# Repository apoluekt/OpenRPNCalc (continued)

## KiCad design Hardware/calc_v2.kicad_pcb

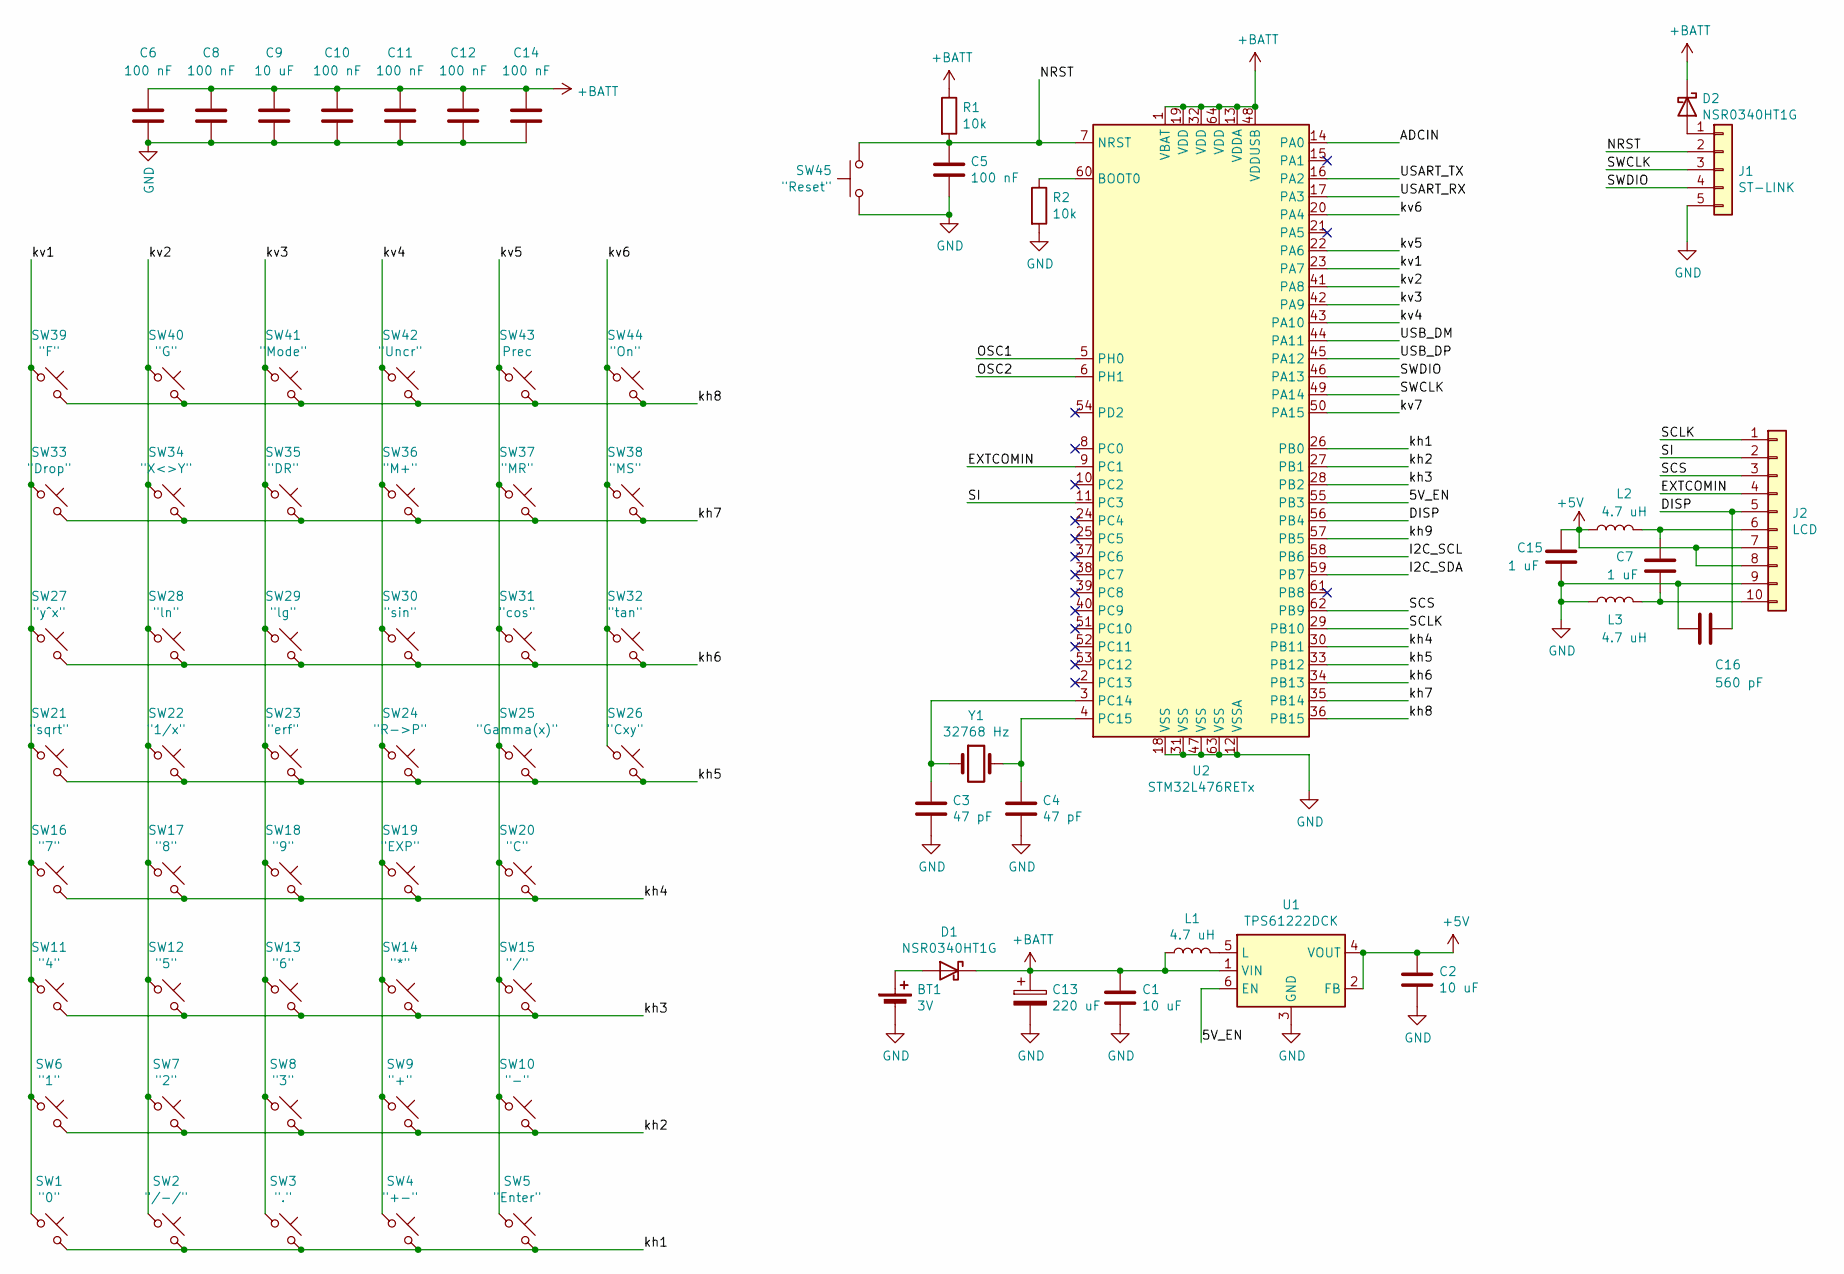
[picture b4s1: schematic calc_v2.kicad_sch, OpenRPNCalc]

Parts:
BT1: 3V; BatteryHolder_Keystone_1057_1x2032
C1, C2, C9: 10 uF; C_0603_1608Metric_Pad1.08x0.95mm_HandSolder
C3, C4: 47 pF; C_0603_1608Metric_Pad1.08x0.95mm_HandSolder
C5, C6, C8, C10, C11, C12, C14: 100 nF; C_0603_1608Metric_Pad1.08x0.95mm_HandSolder
C7, C15: 1 uF; C_0603_1608Metric_Pad1.08x0.95mm_HandSolder
C13: 220 uF; CP_EIA-3528-21_Kemet-B_Pad1.50x2.35mm_HandSolder
C16: 560 pF; C_0603_1608Metric_Pad1.08x0.95mm_HandSolder
D1, D2: NSR0340HT1G; D_0603_1608Metric_Pad1.05x0.95mm_HandSolder
J1: ST-LINK; PinHeader_1x05_P2.54mm_Horizontal
J2: LCD; Molex_1x10_P0.50mm_Horizontal
L1, L2, L3: 4.7 uH; L_0805_2012Metric_Pad1.15x1.40mm_HandSolder
R1, R2: 10k; R_0603_1608Metric_Pad0.98x0.95mm_HandSolder
SW1: "0"; SW_SPST_EVQQ2
SW2: "/-/"; SW_SPST_EVQQ2
SW3: "."; SW_SPST_EVQQ2
SW4: "+-"; SW_SPST_EVQQ2
SW5: "Enter"; SW_SPST_EVQQ2
SW6: "1"; SW_SPST_EVQQ2
SW7: "2"; SW_SPST_EVQQ2
SW8: "3"; SW_SPST_EVQQ2
SW9: "+"; SW_SPST_EVQQ2
SW10: "-"; SW_SPST_EVQQ2
SW11: "4"; SW_SPST_EVQQ2
SW12: "5"; SW_SPST_EVQQ2
SW13: "6"; SW_SPST_EVQQ2
SW14: "*"; SW_SPST_EVQQ2
SW15: "/"; SW_SPST_EVQQ2
SW16: "7"; SW_SPST_EVQQ2
SW17: "8"; SW_SPST_EVQQ2
SW18: "9"; SW_SPST_EVQQ2
SW19: "EXP"; SW_SPST_EVQQ2
SW20: "C"; SW_SPST_EVQQ2
SW21: "sqrt"; SW_SPST_EVQQ2
SW22: "1/x"; SW_SPST_EVQQ2
SW23: "erf"; SW_SPST_EVQQ2
SW24: "R->P"; SW_SPST_EVQQ2
SW25: "Gamma(x)"; SW_SPST_EVQQ2
SW26: "Cxy"; SW_SPST_EVQQ2
SW27: "y^x"; SW_SPST_EVQQ2
SW28: "ln"; SW_SPST_EVQQ2
SW29: "lg"; SW_SPST_EVQQ2
SW30: "sin"; SW_SPST_EVQQ2
SW31: "cos"; SW_SPST_EVQQ2
SW32: "tan"; SW_SPST_EVQQ2
SW33: "Drop"; SW_SPST_EVQQ2
SW34: "X<>Y"; SW_SPST_EVQQ2
SW35: "DR"; SW_SPST_EVQQ2
SW36: "M+"; SW_SPST_EVQQ2
SW37: "MR"; SW_SPST_EVQQ2
SW38: "MS"; SW_SPST_EVQQ2
SW39: "F"; SW_SPST_EVQQ2
SW40: "G"; SW_SPST_EVQQ2
SW41: "Mode"; SW_SPST_EVQQ2
SW42: "Uncr"; SW_SPST_EVQQ2
SW43: Prec; SW_SPST_EVQQ2
SW44: "On"; SW_SPST_EVQQ2
SW45: "Reset"; SW_SPST_EVQQ2
U1: TPS61222DCK; Texas_R-PDSO-G6
U2: STM32L476RETx; LQFP-64_10x10mm_P0.5mm
Y1: 32768 Hz; Crystal_SMD_2012-2Pin_2.0x1.2mm_HandSoldering

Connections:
+5V: C2.1, C15.1, J2.7, J2.8, L2.1, U1.2 (FB), U1.4 (VOUT)
+BATT: C1.1, C6.2, C8.2, C9.2, C10.2, C11.2, C12.2, C13.1, C14.2, D1.1 (K), D2.1 (K), L1.1, R1.1, U1.1 (VIN), U2.1 (VBAT), U2.13 (VDDA), U2.19 (VDD), U2.32 (VDD), U2.48 (VDDUSB), U2.64 (VDD)
/5V_EN: U1.6 (EN), U2.55 (PB3)
/ADCIN: U2.14 (PA0)
/DISP: C16.1, J2.5, U2.56 (PB4)
/EXTCOMIN: J2.4, U2.9 (PC1)
/I2C_SCL: U2.58 (PB6)
/I2C_SDA: U2.59 (PB7)
/NRST: C5.1, J1.2, R1.2, SW45.1, U2.7 (NRST)
/OSC1: U2.5 (PH0)
/OSC2: U2.6 (PH1)
/SCLK: J2.1, U2.29 (PB10)
/SCS: J2.3, U2.62 (PB9)
/SI: J2.2, U2.11 (PC3)
/SWCLK: J1.3, U2.49 (PA14)
/SWDIO: J1.4, U2.46 (PA13)
/USART_RX: U2.17 (PA3)
/USART_TX: U2.16 (PA2)
/USB_DM: U2.44 (PA11)
/USB_DP: U2.45 (PA12)
/kh1: SW1.2, SW2.2, SW3.2, SW4.2, SW5.2, U2.26 (PB0)
/kh2: SW6.2, SW7.2, SW8.2, SW9.2, SW10.2, U2.27 (PB1)
/kh3: SW11.2, SW12.2, SW13.2, SW14.2, SW15.2, U2.28 (PB2)
/kh4: SW16.2, SW17.2, SW18.2, SW19.2, SW20.2, U2.30 (PB11)
/kh5: SW21.2, SW22.2, SW23.2, SW24.2, SW25.2, SW26.2, U2.33 (PB12)
/kh6: SW27.2, SW28.2, SW29.2, SW30.2, SW31.2, SW32.2, U2.34 (PB13)
/kh7: SW33.2, SW34.2, SW35.2, SW36.2, SW37.2, SW38.2, U2.35 (PB14)
/kh8: SW39.2, SW40.2, SW41.2, SW42.2, SW43.2, SW44.2, U2.36 (PB15)
/kh9: U2.57 (PB5)
/kv1: SW1.1, SW6.1, SW11.1, SW16.1, SW21.1, SW27.1, SW33.1, SW39.1, U2.23 (PA7)
/kv2: SW2.1, SW7.1, SW12.1, SW17.1, SW22.1, SW28.1, SW34.1, SW40.1, U2.41 (PA8)
/kv3: SW3.1, SW8.1, SW13.1, SW18.1, SW23.1, SW29.1, SW35.1, SW41.1, U2.42 (PA9)
/kv4: SW4.1, SW9.1, SW14.1, SW19.1, SW24.1, SW30.1, SW36.1, SW42.1, U2.43 (PA10)
/kv5: SW5.1, SW10.1, SW15.1, SW20.1, SW25.1, SW31.1, SW37.1, SW43.1, U2.22 (PA6)
/kv6: SW26.1, SW32.1, SW38.1, SW44.1, U2.20 (PA4)
/kv7: U2.50 (PA15)
GND: BT1.2 (-), C1.2, C2.2, C3.2, C4.2, C5.2, C6.1, C8.1, C9.1, C10.1, C11.1, C12.1, C13.2, C14.1, C15.2, C16.2, J1.5, J2.9, L3.1, R2.2, SW45.2, U1.3 (GND), U2.12 (VSSA), U2.18 (VSS), U2.31 (VSS), U2.47 (VSS), U2.63 (VSS)
unnamed: BT1.1 (+), D1.2 (A)
unnamed: D2.2 (A), J1.1
unnamed: C7.1, J2.6, L2.2
unnamed: C7.2, J2.10, L3.2
unnamed: L1.2, U1.5 (L)
unnamed: R2.1, U2.60 (BOOT0)
unnamed: C3.1, U2.3 (PC14), Y1.1
unnamed: C4.1, U2.4 (PC15), Y1.2

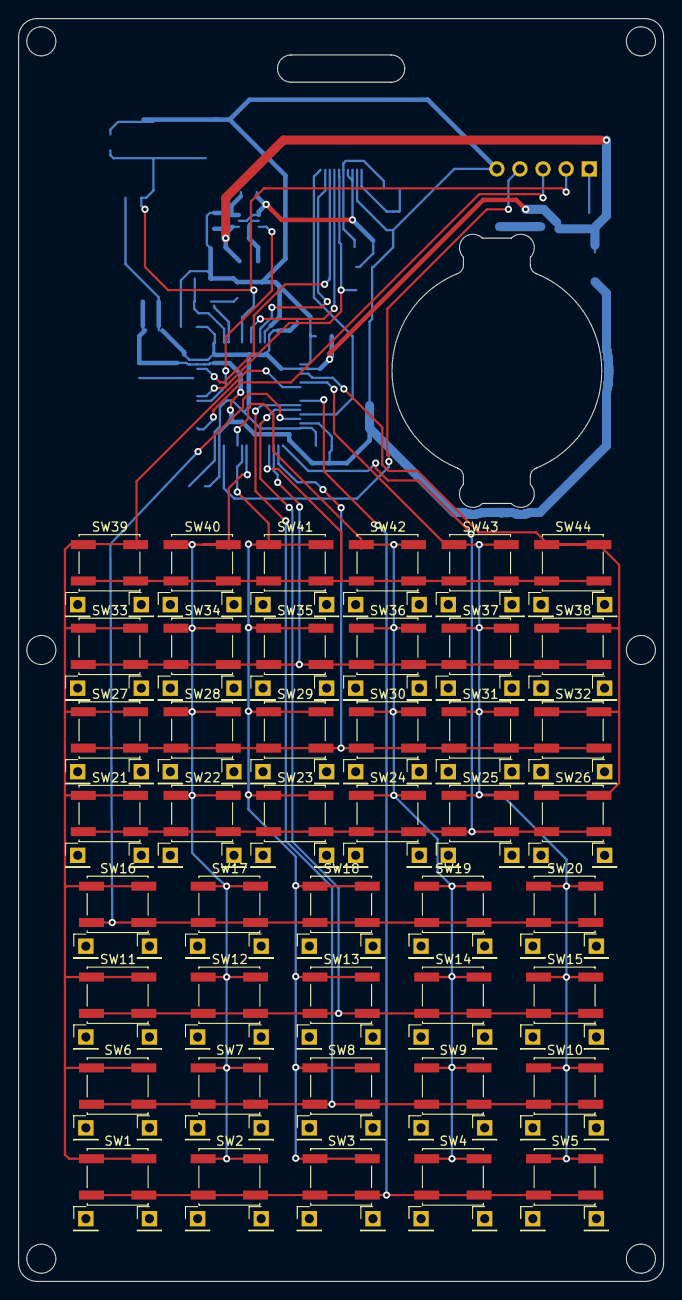
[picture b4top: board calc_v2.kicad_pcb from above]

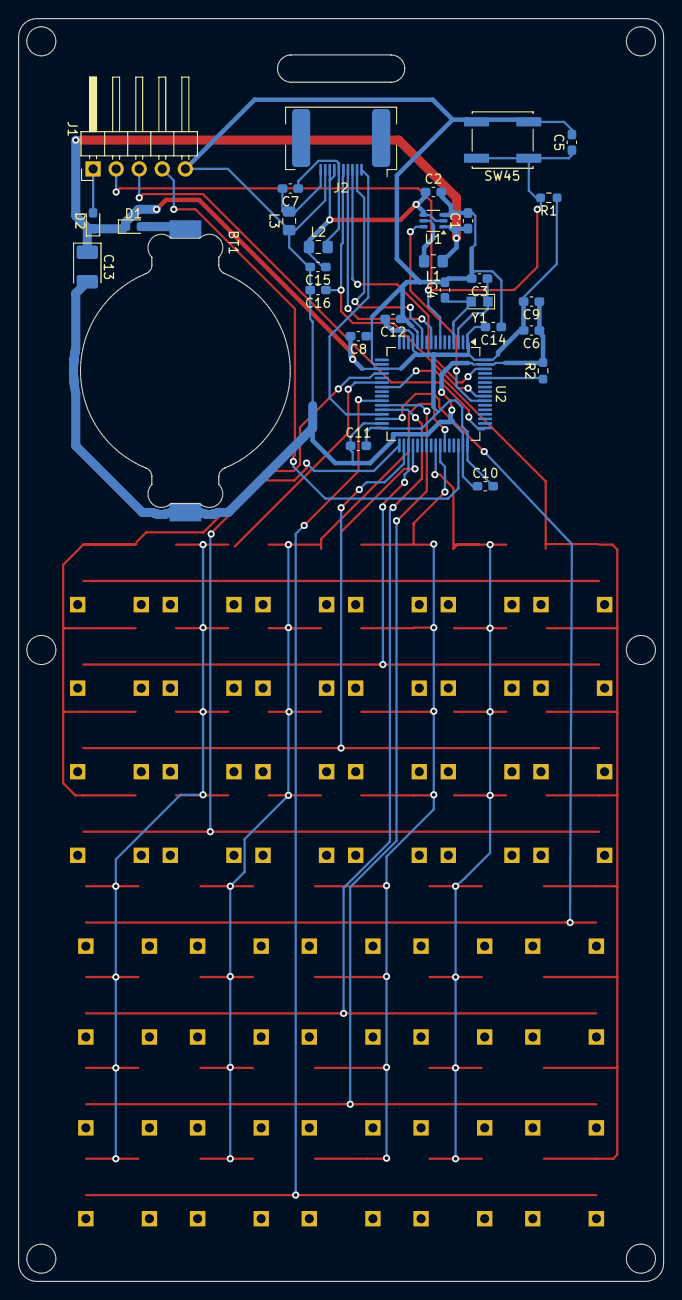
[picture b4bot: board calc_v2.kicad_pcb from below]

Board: 2 copper layers, 71.0 x 139.0 mm, 162 parts (30 on the bottom side), 34 nets.

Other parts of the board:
P1a, P1b, P2a, P2b, P3a, P3b, P4a, P4b, P5a, P5b, P6a, P6b, P7a, P7b, P8a, P8b, P9a, P9b, P10a, P10b, P11a, P11b, P12a, P12b, P13a, P13b, P14a, P14b, P15a, P15b, P16a, P16b, P17a, P17b, P18a, P18b, P19a, P19b, P20a, P20b, P21a, P21b, P22a, P22b, P23a, P23b, P24a, P24b, P25a, P25b, P26a, P26b, P27a, P27b, P28a, P28b, P29a, P29b, P30a, P30b, P31a, P31b, P32a, P32b, P33a, P33b, P34a, P34b, P35a, P35b, P36a, P36b, P37a, P37b, P38a, P38b, P39a, P39b, P40a, P40b, P41a, P41b, P42a, P42b, P43a, P43b, P44a, P44b: PinHeader_1x01_P2.54mm_Vertical

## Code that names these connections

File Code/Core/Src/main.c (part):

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		if (keycode == 54 && off && last_keycode == 0) {  // Calculator was OFF and the ON button was pressed
			HAL_GPIO_WritePin(GPIOA, GPIO_PIN_15, GPIO_PIN_SET); // 5V booster enable
			HAL_Delay(1); // Wait while 5V rises
			HAL_GPIO_WritePin(GPIOA, GPIO_PIN_10, GPIO_PIN_SET); // DISP signal to "ON"
			delay_us(30);
			keycode = 0;
			off = 0;
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
			if (!ret) {  // OFF command received
				delay_us(30);
				HAL_GPIO_WritePin(GPIOA, GPIO_PIN_10, GPIO_PIN_RESET);  // DISP signal to "OFF"
				delay_us(30);
				HAL_GPIO_WritePin(GPIOA, GPIO_PIN_9, GPIO_PIN_RESET);   // EXTCOMIN signal of "OFF"
				HAL_GPIO_WritePin(GPIOA, GPIO_PIN_15, GPIO_PIN_RESET);  // 5V booster disable
				off = 1;
			}
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  /*Configure GPIO pin Output Level */
  HAL_GPIO_WritePin(GPIOD, GPIO_PIN_2, GPIO_PIN_RESET);

  /*Configure GPIO pins : PC13 PC14 PC15 PC8
                           PC9 PC10 PC11 PC12 */
  GPIO_InitStruct.Pin = GPIO_PIN_13|GPIO_PIN_14|GPIO_PIN_15|GPIO_PIN_8
                          |GPIO_PIN_9|GPIO_PIN_10|GPIO_PIN_11|GPIO_PIN_12;
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  GPIO_InitStruct.Pull = GPIO_NOPULL;
  HAL_GPIO_Init(GPIOC, &GPIO_InitStruct);

  /*Configure GPIO pins : PH0 PH1 PH3 */
  GPIO_InitStruct.Pin = GPIO_PIN_0|GPIO_PIN_1|GPIO_PIN_3;
  GPIO_InitStruct.Mode = GPIO_MODE_ANALOG;
  GPIO_InitStruct.Pull = GPIO_NOPULL;
  HAL_GPIO_Init(GPIOH, &GPIO_InitStruct);

  /*Configure GPIO pin : PC0 */
  GPIO_InitStruct.Pin = GPIO_PIN_0;
  GPIO_InitStruct.Mode = GPIO_MODE_OUTPUT_PP;
  GPIO_InitStruct.Pull = GPIO_NOPULL;
  GPIO_InitStruct.Speed = GPIO_SPEED_FREQ_VERY_HIGH;
  HAL_GPIO_Init(GPIOC, &GPIO_InitStruct);

  /*Configure GPIO pins : PC2 PC6 */
  GPIO_InitStruct.Pin = GPIO_PIN_2|GPIO_PIN_6;
  GPIO_InitStruct.Mode = GPIO_MODE_INPUT;
  GPIO_InitStruct.Pull = GPIO_PULLUP;
  HAL_GPIO_Init(GPIOC, &GPIO_InitStruct);

  /*Configure GPIO pin : PC3 */
  GPIO_InitStruct.Pin = GPIO_PIN_3;
  GPIO_InitStruct.Mode = GPIO_MODE_INPUT;
  GPIO_InitStruct.Pull = GPIO_NOPULL;
  HAL_GPIO_Init(GPIOC, &GPIO_InitStruct);

  /*Configure GPIO pins : PA0 PA2 PA3 PA4
                           PA5 PA8 */
  GPIO_InitStruct.Pin = GPIO_PIN_0|GPIO_PIN_2|GPIO_PIN_3|GPIO_PIN_4
                          |GPIO_PIN_5|GPIO_PIN_8;
  GPIO_InitStruct.Mode = GPIO_MODE_OUTPUT_OD;
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  GPIO_InitStruct.Speed = GPIO_SPEED_FREQ_LOW;
  HAL_GPIO_Init(GPIOA, &GPIO_InitStruct);

  /*Configure GPIO pins : PA1 PA6 PA7 PA11
                           PA12 */
  GPIO_InitStruct.Pin = GPIO_PIN_1|GPIO_PIN_6|GPIO_PIN_7|GPIO_PIN_11
                          |GPIO_PIN_12;
  GPIO_InitStruct.Mode = GPIO_MODE_ANALOG;
  GPIO_InitStruct.Pull = GPIO_NOPULL;
  HAL_GPIO_Init(GPIOA, &GPIO_InitStruct);

  /*Configure GPIO pins : PB0 PB1 PB2 PB13
                           PB14 PB3 PB4 PB5 */
  GPIO_InitStruct.Pin = GPIO_PIN_0|GPIO_PIN_1|GPIO_PIN_2|GPIO_PIN_13
                          |GPIO_PIN_14|GPIO_PIN_3|GPIO_PIN_4|GPIO_PIN_5;
  GPIO_InitStruct.Mode = GPIO_MODE_IT_FALLING;
  GPIO_InitStruct.Pull = GPIO_NOPULL;
  HAL_GPIO_Init(GPIOB, &GPIO_InitStruct);

  /*Configure GPIO pin : PB15 */
  GPIO_InitStruct.Pin = GPIO_PIN_15;
  GPIO_InitStruct.Mode = GPIO_MODE_IT_RISING;
  GPIO_InitStruct.Pull = GPIO_NOPULL;
  HAL_GPIO_Init(GPIOB, &GPIO_InitStruct);

  /*Configure GPIO pin : PC7 */
  GPIO_InitStruct.Pin = GPIO_PIN_7;
  GPIO_InitStruct.Mode = GPIO_MODE_OUTPUT_OD;
  GPIO_InitStruct.Pull = GPIO_NOPULL;
  GPIO_InitStruct.Speed = GPIO_SPEED_FREQ_LOW;
  HAL_GPIO_Init(GPIOC, &GPIO_InitStruct);

  /*Configure GPIO pins : PA9 PA10 */
  GPIO_InitStruct.Pin = GPIO_PIN_9|GPIO_PIN_10;
  GPIO_InitStruct.Mode = GPIO_MODE_OUTPUT_PP;
  GPIO_InitStruct.Pull = GPIO_NOPULL;
  GPIO_InitStruct.Speed = GPIO_SPEED_FREQ_VERY_HIGH;
  HAL_GPIO_Init(GPIOA, &GPIO_InitStruct);

  /*Configure GPIO pin : PA15 */
  GPIO_InitStruct.Pin = GPIO_PIN_15;
  GPIO_InitStruct.Mode = GPIO_MODE_OUTPUT_PP;
  GPIO_InitStruct.Pull = GPIO_NOPULL;
  GPIO_InitStruct.Speed = GPIO_SPEED_FREQ_LOW;
  HAL_GPIO_Init(GPIOA, &GPIO_InitStruct);

  /*Configure GPIO pin : PD2 */
  GPIO_InitStruct.Pin = GPIO_PIN_2;
  GPIO_InitStruct.Mode = GPIO_MODE_OUTPUT_PP;
  GPIO_InitStruct.Pull = GPIO_NOPULL;
  GPIO_InitStruct.Speed = GPIO_SPEED_FREQ_LOW;
  HAL_GPIO_Init(GPIOD, &GPIO_InitStruct);

  /*Configure GPIO pins : PB6 PB7 */
  GPIO_InitStruct.Pin = GPIO_PIN_6|GPIO_PIN_7;
  GPIO_InitStruct.Mode = GPIO_MODE_ANALOG;
  GPIO_InitStruct.Pull = GPIO_NOPULL;
  HAL_GPIO_Init(GPIOB, &GPIO_InitStruct);

  /*Configure GPIO pin : PB8 */
  GPIO_InitStruct.Pin = GPIO_PIN_8;
  GPIO_InitStruct.Mode = GPIO_MODE_IT_FALLING;
  GPIO_InitStruct.Pull = GPIO_PULLUP;
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	if (!off) {
		timeout_counter++;
		if (timeout_counter > OFF_TIMEOUT) {
			HAL_GPIO_WritePin(GPIOA, GPIO_PIN_10, GPIO_PIN_RESET);  // DISP signal to "OFF"
			HAL_GPIO_WritePin(GPIOA, GPIO_PIN_9, GPIO_PIN_RESET);   // EXTCOMIN signal of "OFF"
			HAL_GPIO_WritePin(GPIOA, GPIO_PIN_15, GPIO_PIN_RESET);  // 5V booster disable
			off = 1;
		}
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
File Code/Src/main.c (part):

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		keycode = scan_keyboard();

		if (keycode == 48 && off && last_keycode == 0) {  // Calculator was OFF and the ON button was pressed
			HAL_GPIO_WritePin(GPIOB, GPIO_PIN_4, GPIO_PIN_SET); // DISP signal to "ON"
			HAL_GPIO_WritePin(GPIOB, GPIO_PIN_3, GPIO_PIN_SET); // 5V booster enable
			keycode = 0;
			off = 0;
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			}

			if (!ret) {  // OFF command received
				HAL_GPIO_WritePin(GPIOB, GPIO_PIN_4, GPIO_PIN_RESET);  // DISP signal to "OFF"
				HAL_GPIO_WritePin(GPIOC, GPIO_PIN_1, GPIO_PIN_RESET);  // EXTIN signal of "OFF"
				HAL_GPIO_WritePin(GPIOB, GPIO_PIN_3, GPIO_PIN_RESET);  // 5V booster disable
				off = 1;
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  HAL_GPIO_WritePin(GPIOB, GPIO_PIN_3|GPIO_PIN_4|GPIO_PIN_5|GPIO_PIN_6
                          |GPIO_PIN_7|GPIO_PIN_9, GPIO_PIN_RESET);

  /*Configure GPIO pins : PC13 PC0 PC1 PC2
                           PC4 PC5 PC6 PC7
                           PC8 PC9 PC10 PC11
                           PC12 */
  GPIO_InitStruct.Pin = GPIO_PIN_13|GPIO_PIN_0|GPIO_PIN_1|GPIO_PIN_2
                          |GPIO_PIN_4|GPIO_PIN_5|GPIO_PIN_6|GPIO_PIN_7
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  GPIO_InitStruct.Speed = GPIO_SPEED_FREQ_LOW;
  HAL_GPIO_Init(GPIOC, &GPIO_InitStruct);

  /*Configure GPIO pins : PA0 PA1 PA2 PA3
                           PA5 PA11 PA12 PA15 */
  GPIO_InitStruct.Pin = GPIO_PIN_0|GPIO_PIN_1|GPIO_PIN_2|GPIO_PIN_3
                          |GPIO_PIN_5|GPIO_PIN_11|GPIO_PIN_12|GPIO_PIN_15;
  GPIO_InitStruct.Mode = GPIO_MODE_OUTPUT_PP;
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  GPIO_InitStruct.Speed = GPIO_SPEED_FREQ_LOW;
  HAL_GPIO_Init(GPIOA, &GPIO_InitStruct);

  /*Configure GPIO pins : PA4 PA6 PA7 PA8
                           PA9 PA10 */
  GPIO_InitStruct.Pin = GPIO_PIN_4|GPIO_PIN_6|GPIO_PIN_7|GPIO_PIN_8
                          |GPIO_PIN_9|GPIO_PIN_10;
  GPIO_InitStruct.Mode = GPIO_MODE_OUTPUT_OD;
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  GPIO_InitStruct.Speed = GPIO_SPEED_FREQ_LOW;
  HAL_GPIO_Init(GPIOA, &GPIO_InitStruct);

  /*Configure GPIO pins : PB0 PB1 PB2 PB11
                           PB12 PB13 PB14 PB15 */
  GPIO_InitStruct.Pin = GPIO_PIN_0|GPIO_PIN_1|GPIO_PIN_2|GPIO_PIN_11
                          |GPIO_PIN_12|GPIO_PIN_13|GPIO_PIN_14|GPIO_PIN_15;
  GPIO_InitStruct.Mode = GPIO_MODE_IT_FALLING;
  GPIO_InitStruct.Pull = GPIO_PULLUP;
  HAL_GPIO_Init(GPIOB, &GPIO_InitStruct);

  /*Configure GPIO pins : PB3 PB4 PB5 PB6
                           PB7 PB9 */
  GPIO_InitStruct.Pin = GPIO_PIN_3|GPIO_PIN_4|GPIO_PIN_5|GPIO_PIN_6
                          |GPIO_PIN_7|GPIO_PIN_9;
  GPIO_InitStruct.Mode = GPIO_MODE_OUTPUT_PP;
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  GPIO_InitStruct.Speed = GPIO_SPEED_FREQ_LOW;
  HAL_GPIO_Init(GPIOB, &GPIO_InitStruct);

  /*Configure GPIO pin : PB8 */
  GPIO_InitStruct.Pin = GPIO_PIN_8;
  GPIO_InitStruct.Mode = GPIO_MODE_INPUT;
  GPIO_InitStruct.Pull = GPIO_PULLUP;
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	if (!off) {
		timeout_counter++;
		if (timeout_counter > OFF_TIMEOUT) {
			HAL_GPIO_WritePin(GPIOB, GPIO_PIN_4, GPIO_PIN_RESET);  // DISP signal to "OFF"
			HAL_GPIO_WritePin(GPIOC, GPIO_PIN_1, GPIO_PIN_RESET);  // EXTIN signal of "OFF"
			HAL_GPIO_WritePin(GPIOB, GPIO_PIN_3, GPIO_PIN_RESET);  // 5V booster disable
			off = 1;
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
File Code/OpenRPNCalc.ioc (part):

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Mcu.Name=STM32U385RGTxQ
Mcu.Package=LQFP64
Mcu.UserName=STM32U385RGTxQ
PA0.GPIOParameters=GPIO_PuPd,GPIO_ModeDefaultOutputPP
PA0.GPIO_ModeDefaultOutputPP=GPIO_MODE_OUTPUT_OD
PA0.GPIO_PuPd=GPIO_NOPULL
PA0.Signal=GPIO_Output
PA10.GPIOParameters=GPIO_Speed
PA10.GPIO_Speed=GPIO_SPEED_FREQ_VERY_HIGH
PA10.Signal=GPIO_Output
PA13\ (JTMS/SWDIO).Mode=Serial_Wire
PA13\ (JTMS/SWDIO).Signal=DEBUG_JTMS-SWDIO
PA14\ (JTCK/SWCLK).Mode=Serial_Wire
PA14\ (JTCK/SWCLK).Signal=DEBUG_JTCK-SWCLK
PA15\ (JTDI).Signal=GPIO_Output
PA2.GPIOParameters=GPIO_PuPd,GPIO_ModeDefaultOutputPP
PA2.GPIO_ModeDefaultOutputPP=GPIO_MODE_OUTPUT_OD
PA2.GPIO_PuPd=GPIO_NOPULL
PA2.Signal=GPIO_Output
PA3.GPIOParameters=GPIO_PuPd,GPIO_ModeDefaultOutputPP
PA3.GPIO_ModeDefaultOutputPP=GPIO_MODE_OUTPUT_OD
PA3.GPIO_PuPd=GPIO_NOPULL
PA3.Signal=GPIO_Output
PA4.GPIOParameters=GPIO_PuPd,GPIO_ModeDefaultOutputPP
PA4.GPIO_ModeDefaultOutputPP=GPIO_MODE_OUTPUT_OD
PA4.GPIO_PuPd=GPIO_NOPULL
PA4.Signal=GPIO_Output
PA5.GPIOParameters=GPIO_PuPd,GPIO_ModeDefaultOutputPP
PA5.GPIO_ModeDefaultOutputPP=GPIO_MODE_OUTPUT_OD
PA5.GPIO_PuPd=GPIO_NOPULL
PA5.Signal=GPIO_Output
PA8.GPIOParameters=GPIO_PuPd,GPIO_ModeDefaultOutputPP
PA8.GPIO_ModeDefaultOutputPP=GPIO_MODE_OUTPUT_OD
PA8.GPIO_PuPd=GPIO_NOPULL
PA8.Signal=GPIO_Output
PA9.GPIOParameters=GPIO_Speed
PA9.GPIO_Speed=GPIO_SPEED_FREQ_VERY_HIGH
PA9.Signal=GPIO_Output
PB0.GPIOParameters=GPIO_ModeDefaultEXTI
PB0.GPIO_ModeDefaultEXTI=GPIO_MODE_IT_FALLING
PB0.Signal=GPXTI0
PB1.GPIOParameters=GPIO_ModeDefaultEXTI
PB1.GPIO_ModeDefaultEXTI=GPIO_MODE_IT_FALLING
PB1.Signal=GPXTI1
PB10.GPIOParameters=GPIO_Speed
PB10.GPIO_Speed=GPIO_SPEED_FREQ_VERY_HIGH
PB10.Mode=TX_Only_Simplex_Unidirect_Master
PB10.Signal=SPI2_SCK
PB13.GPIOParameters=GPIO_ModeDefaultEXTI
PB13.GPIO_ModeDefaultEXTI=GPIO_MODE_IT_FALLING
PB13.Signal=GPXTI13
PB14.GPIOParameters=GPIO_ModeDefaultEXTI
PB14.GPIO_ModeDefaultEXTI=GPIO_MODE_IT_FALLING
PB14.Signal=GPXTI14
PB15.Signal=GPXTI15
PB2.GPIOParameters=GPIO_ModeDefaultEXTI
PB2.GPIO_ModeDefaultEXTI=GPIO_MODE_IT_FALLING
PB2.Signal=GPXTI2
PB3\ (JTDO/TRACESWO).GPIOParameters=GPIO_ModeDefaultEXTI
PB3\ (JTDO/TRACESWO).GPIO_ModeDefaultEXTI=GPIO_MODE_IT_FALLING
PB3\ (JTDO/TRACESWO).Signal=GPXTI3
PB4\ (NJTRST).GPIOParameters=GPIO_ModeDefaultEXTI
PB4\ (NJTRST).GPIO_ModeDefaultEXTI=GPIO_MODE_IT_FALLING
PB4\ (NJTRST).Signal=GPXTI4
PB5.GPIOParameters=GPIO_ModeDefaultEXTI
PB5.GPIO_ModeDefaultEXTI=GPIO_MODE_IT_FALLING
PB5.Signal=GPXTI5
PB8.GPIOParameters=GPIO_PuPd,GPIO_ModeDefaultEXTI
PB8.GPIO_ModeDefaultEXTI=GPIO_MODE_IT_FALLING
PB8.GPIO_PuPd=GPIO_PULLUP
PB8.Signal=GPXTI8
PC0.GPIOParameters=GPIO_Speed
PC0.GPIO_Speed=GPIO_SPEED_FREQ_VERY_HIGH
PC0.Signal=GPIO_Output
PC1.GPIOParameters=GPIO_Speed
PC1.GPIO_Speed=GPIO_SPEED_FREQ_VERY_HIGH
PC1.Mode=TX_Only_Simplex_Unidirect_Master
PC1.Signal=SPI2_MOSI
PC2.GPIOParameters=GPIO_PuPd
PC2.GPIO_PuPd=GPIO_PULLUP
PC2.Signal=GPIO_Input
PC3.GPIOParameters=GPIO_PuPd
PC3.GPIO_PuPd=GPIO_NOPULL
PC3.Signal=GPIO_Input
PC6.GPIOParameters=GPIO_PuPd
PC6.GPIO_PuPd=GPIO_PULLUP
PC6.Signal=GPIO_Input
PC7.GPIOParameters=PinState,GPIO_PuPd,GPIO_ModeDefaultOutputPP
PC7.GPIO_ModeDefaultOutputPP=GPIO_MODE_OUTPUT_OD
PC7.GPIO_PuPd=GPIO_NOPULL
PC7.PinState=GPIO_PIN_SET
PC7.Signal=GPIO_Output
PC8.Signal=GPIO_Analog
PD2.Signal=GPIO_Output
RCC.HSE_VALUE=16000000
RCC.SYSCLKFreq_VALUE=16000000
RCC.SYSCLKSource=RCC_SYSCLKSOURCE_HSI
board=custom

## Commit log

2021-05-23 Add photos, keyboard sticker, credits
2021-05-23 Add schematic in PNG and PDF
2021-05-24 Update key stickers
2021-05-24 Update key sticker
2021-05-24 Modify keys layout; add gamma and loggamma functions
2021-05-28 Update stickers; Add functions for relativistic kinematics
2021-06-02 C(n,k), P(n,k), significance functions
2021-06-19 STOP2 mode in standby; new photos
2021-06-19 Fix schematic to fit the one actually implemented
2021-06-21 Poisson PDF and chi2 probability
2021-06-21 Stickers for Poisson and chi2
2021-06-25 ROT-Up and ROT-Down; Uncertainties for power and root
2025-01-01 Rev. 2
2025-01-01 Firmware Rev. 2
2025-01-01 Add firmware file
2025-01-01 Add KiCAD images
2025-02-01 Add photos
2025-02-01 Update PCB 3D models
2025-02-01 Add gerbers
2025-02-01 Add OpenSCAD files
2025-02-01 Add schematic png
2025-02-01 Add images of 3D printed parts
2025-02-14 Add functions; keyboard scan bugfixes
2025-02-20 Add emulator
2025-02-20 Infinite stack
2025-03-07 rev 3
2025-03-07 Add phtoos
2025-03-09 Speed up text output
2025-03-28 Rev 3.1
2025-03-28 Update firmware binary and emulator
2025-04-24 Rev 4 schematics
2025-04-25 Update rev 4 schematics
2025-04-27 Update component names in schematic, add PDBs
2025-04-27 Remove rev3 images, add renders
2025-04-27 Minor schematic cleanup
2025-04-30 Production files
2025-05-03 Update enter stab; add new renders
2025-05-06 Update battery holder part name
2025-05-07 Update schematics.md: add BOM
2025-05-07 Update production files
2025-05-20 Bugfix 4.0; added HP48 layout
2025-05-21 Use section headers in documentation
    Section headers can be linked, which is more convenient to refer to specific sections in the documentation
2025-05-29 Update firmware code
2025-06-08 Add Hardware/python dir
